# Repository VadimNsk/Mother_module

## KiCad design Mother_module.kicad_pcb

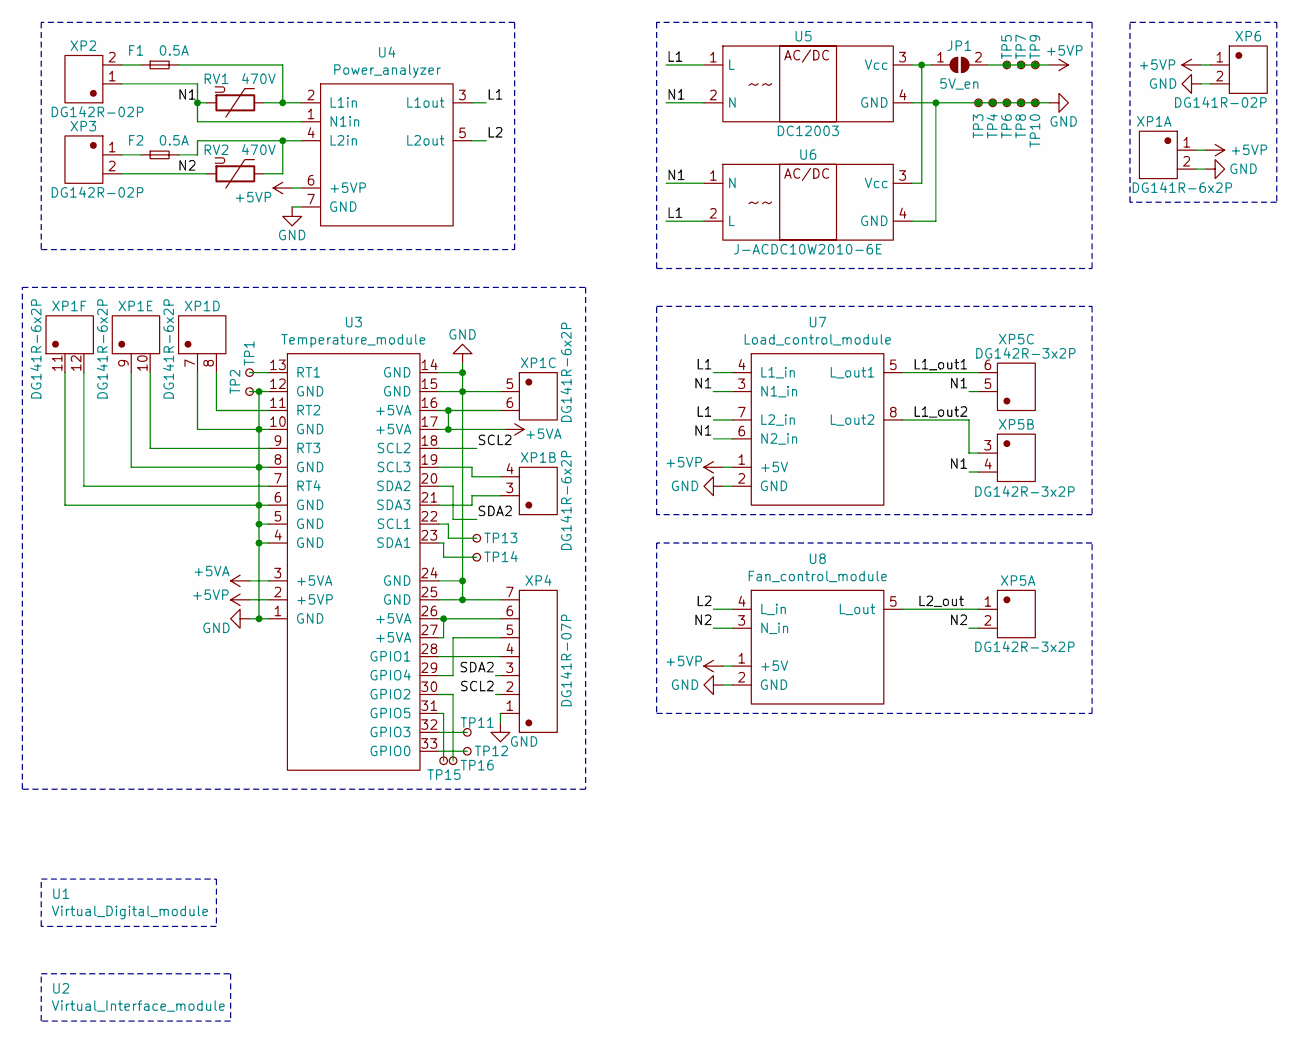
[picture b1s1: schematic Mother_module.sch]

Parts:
F1, F2: 0.5A; FC-05C-E_4x15
JP1: 5V_en; SolderJumper-2_P1.3mm_Open_TrianglePad1.0x1.5mm
RV1, RV2: 470V; RV_Disc_D7mm_W4.5mm_P5mm
TP1, TP2, TP3, TP4, TP5, TP6, TP7, TP8, TP9, TP10, TP11, TP12, TP13, TP14, TP15, TP16: TestPoint_Small; TestPoint_THTPad_D2.0mm_Drill1.0mm
U1: Virtual_Digital_module
U2: Virtual_Interface_module
U3: Temperature_module
U4: Power_analyzer
U5: DC12003
U6: J-ACDC10W2010-6E
U7: Load_control_module
U8: Fan_control_module
XP1: DG141R-6x2P; DG141R-2.54-12P-14-00A(H)
XP2, XP3: DG142R-02P; XY122R-5.08-02P-14
XP4: DG141R-07P; DG141R-2.54-07P-14-00A(H)
XP5: DG142R-3x2P; XY122R-5.08-06P-14
XP6: DG141R-02P; DG141R-2.54-02P-14-00A(H)

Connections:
+5VA: U3.3 (+5VA), U3.16 (+5VA), U3.17 (+5VA), XP1.6
+5VP: JP1.2 (B), TP5.1, TP7.1, TP9.1, U3.2 (+5VP), U4.6 (+5VP), U7.1 (+5V), U8.1 (+5V), XP1.1, XP6.1
/L1: U4.3 (L1out), U5.1 (L), U6.2 (L), U7.4 (L1_in), U7.7 (L2_in)
/L1_out1: U7.5 (L_out1), XP5.6
/L1_out2: U7.8 (L_out2), XP5.3
/L2: U4.5 (L2out), U8.4 (L_in)
/L2_out: U8.5 (L_out), XP5.1
/N1: RV1.2, U4.1 (N1in), U5.2 (N), U6.1 (N), U7.3 (N1_in), U7.6 (N2_in), XP2.1, XP5.4, XP5.5
/N2: RV2.2, U8.3 (N_in), XP3.2, XP5.2
/SCL2: U3.18 (SCL2), XP4.2
/SDA2: U3.20 (SDA2), XP4.3
GND: TP2.1, TP3.1, TP4.1, TP6.1, TP8.1, TP10.1, U3.1 (GND), U3.4 (GND), U3.5 (GND), U3.6 (GND), U3.8 (GND), U3.10 (GND), U3.12 (GND), U3.14 (GND), U3.15 (GND), U3.24 (GND), U3.25 (GND), U4.7 (GND), U5.4 (GND), U6.4 (GND), U7.2 (GND), U8.2 (GND), XP1.2, XP1.5, XP1.7, XP1.9, XP1.11, XP4.1, XP4.7, XP6.2
unnamed: F1.1, XP2.2
unnamed: F1.2, RV1.1, U4.2 (L1in)
unnamed: F2.1, XP3.1
unnamed: F2.2, RV2.1, U4.4 (L2in)
unnamed: JP1.1 (A), U5.3 (Vcc), U6.3 (Vcc)
unnamed: TP1.1, U3.13 (RT1)
unnamed: TP11.1, U3.32 (GPIO3)
unnamed: TP12.1, U3.33 (GPIO0)
unnamed: TP13.1, U3.22 (SCL1)
unnamed: TP14.1, U3.23 (SDA1)
unnamed: TP15.1, U3.31 (GPIO5)
unnamed: TP16.1, U3.30 (GPIO2)
unnamed: U3.7 (RT4), XP1.12
unnamed: U3.9 (RT3), XP1.10
unnamed: U3.11 (RT2), XP1.8
unnamed: U3.19 (SCL3), XP1.4
unnamed: U3.21 (SDA3), XP1.3
unnamed: U3.26 (+5VA), U3.27 (+5VA), XP4.6
unnamed: U3.28 (GPIO1), XP4.4
unnamed: U3.29 (GPIO4), XP4.5

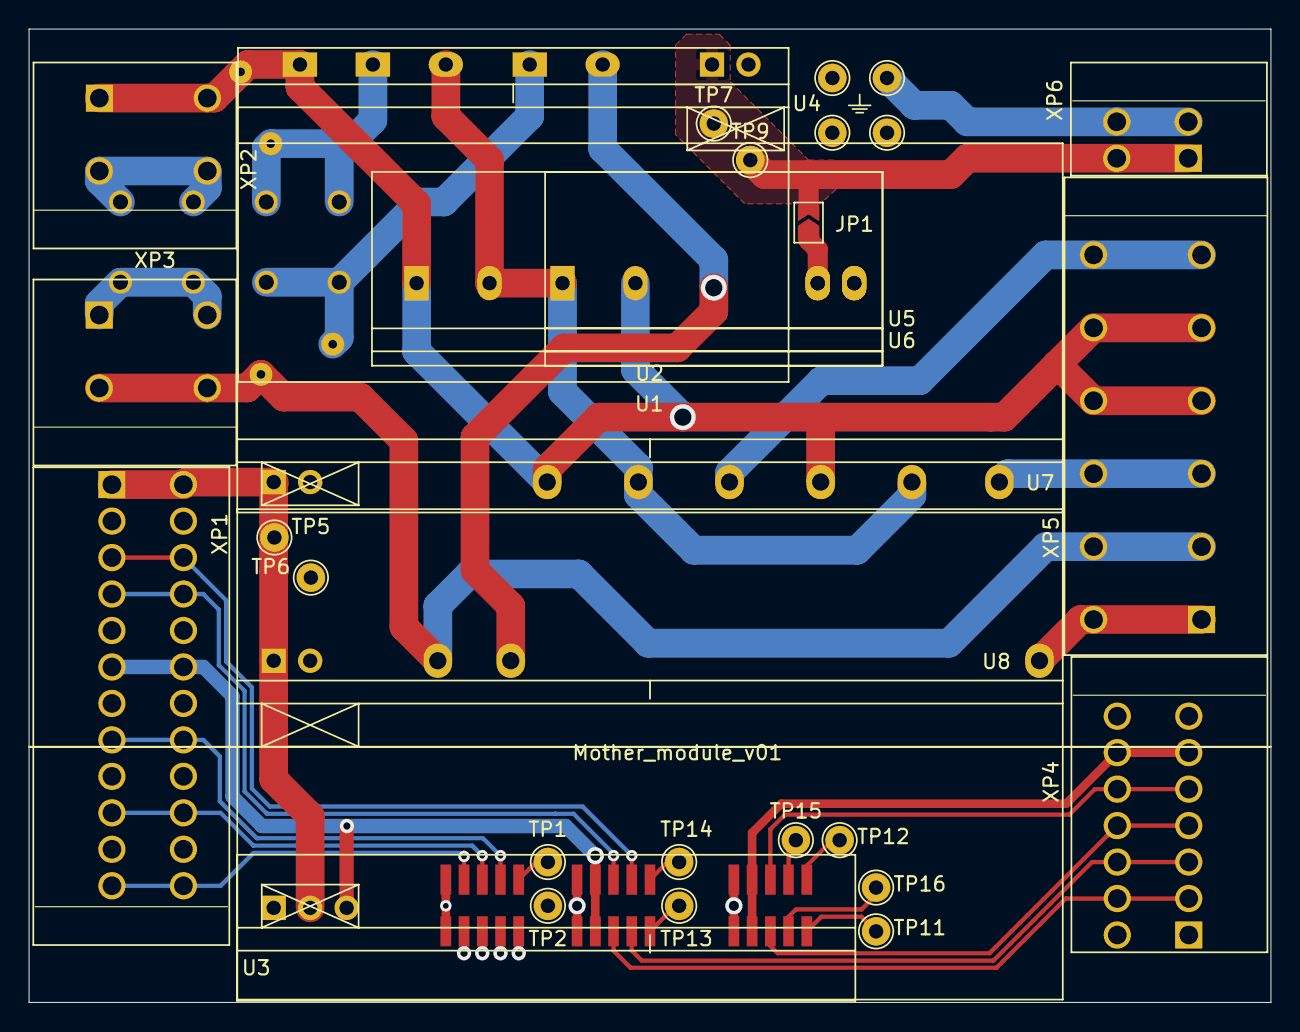
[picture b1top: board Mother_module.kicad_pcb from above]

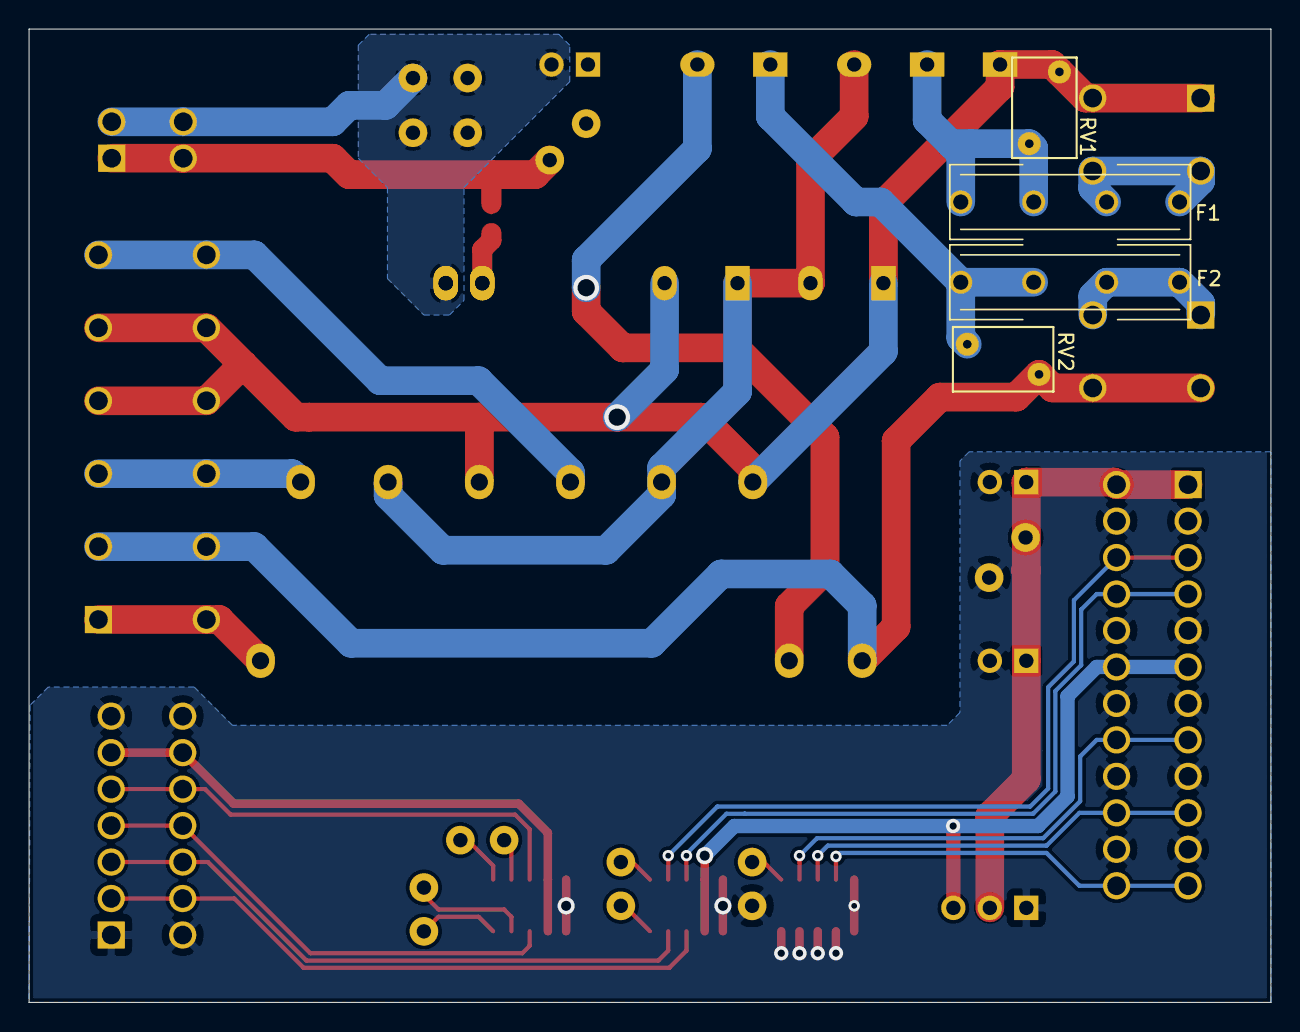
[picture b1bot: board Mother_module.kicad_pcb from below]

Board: 2 copper layers, 86.5 x 67.8 mm, 35 parts (4 on the bottom side), 32 nets.

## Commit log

2021-07-04 Добавлены файлы схемы, трассировки, список комплектующих и гербера
